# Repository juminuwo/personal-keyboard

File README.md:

# Personal Split Keyboard

A 33-key split ergonomic keyboard designed with Ergogen and KiCad.

## PCB Preview

| Left Half | Right Half |
|-----------|------------|
|  |  |

## Layout

```
Left Hand (17 keys)                    Right Hand (16 keys)

     Q     W     E     R     T              Y     U     I     O
     A   ALT_S CTL_D SFT_F   G            SFT_H CTL_J ALT_K   L     P
   GUI_Z   X     C     V     B              N     M     ,   GUI_.   /
               [LOWER] [ENTER]          [SPACE] [RAISE]
```

- 5x3 matrix per hand with staggered columns
- Right pinky top key removed (reduced pinky strain)
- 2 thumb keys per hand with splay
- Home row mods on S, D, F, H, J, K, Z, .

## Parts List

| Component | Quantity | Notes |
|-----------|----------|-------|
| **Switches** | | |
| Kailh Choc v1 switches | 33 | Low-profile, PG1350 |
| Kailh Choc hotswap sockets | 33 | CPG135001S30 |
| **Keycaps** | | |
| Choc-compatible keycaps | 33 | 18mm x 17mm spacing |
| **Electronics** | | |
| RP2040 Pro Micro | 2 | Recommended (has onboard reset/boot buttons) |
| 1N4148 diodes | 33 | Through-hole or SMD (SOD-123) |
| TRRS jack (PJ-320A) | 2 | 4-pole, for split communication |
| Tactile reset button | 2 | Optional - SMD 5.2x5.2mm (SKQGABE010) |
| **Cables & Hardware** | | |
| TRRS cable | 1 | 4-pole, any length |
| USB-C cable | 1 | For connecting to computer |
| Rubber feet | 8-10 | Self-adhesive silicone bumpers |

## PCB Specifications

| Spec | Value |
|------|-------|
| Key spacing (X) | 18mm (standard Choc) |
| Key spacing (Y) | 17mm (standard Choc) |
| Switch cutout | 13.8mm x 13.8mm |
| PCB thickness | 1.6mm (standard) |
| Layers | 2 (F.Cu, B.Cu) |

### Column Stagger

**Left Hand:**
| Finger | Stagger |
|--------|---------|
| Pinky | 0mm (baseline) |
| Ring | +5mm |
| Middle | +2.5mm |
| Index | -2.5mm |
| Inner | -2.5mm |

**Right Hand (intentionally different due to hand injury):**
| Finger | Stagger |
|--------|---------|
| Inner | +2.5mm |
| Index | +2.5mm |
| Middle | -2.5mm |
| Ring | -5mm |
| Pinky | 0mm (baseline) |

### Thumb Cluster

- Offset 27mm below index finger
- Outer thumb: 10 degrees splay
- Inner thumb: 5 degrees splay

## Build Instructions

### 1. Generate PCB Files

```bash
npx ergogen keyboard.yaml -o output
```

### 2. Open in KiCad

Open `output/pcbs/left_pcb.kicad_pcb` and `output/pcbs/right_pcb.kicad_pcb` in KiCad.

### 3. Route Traces

Complete the PCB routing in KiCad:
- Route columns on B.Cu (bottom layer)
- Route rows on F.Cu (top layer)
- Add ground pour on B.Cu
- Run DRC to check for errors

### 4. Manufacturing

Export Gerber files and submit to a PCB manufacturer:
- JLCPCB (budget, ships from China)
- Aisler (EU-based, no customs for UK/EU)
- PCBWay

### 5. Assembly Order

1. Solder diodes (observe polarity, bottom side)
2. Solder hotswap sockets (bottom side)
3. Solder TRRS jack
4. Solder reset button (optional)
5. Solder Pro Micro headers or directly
6. Insert switches into hotswap sockets
7. Add keycaps

## Firmware

This keyboard uses QMK firmware, based on my [Sofle personal keymap](https://github.com/juminuwo/sofle-personal-keymap).

### QMK File Structure

```
qmk/
├── config.h              # Keyboard-level config
├── info.json             # Keyboard definition (pins, matrix)
├── rules.mk              # Build rules
└── keymaps/
    └── default/
        ├── config.h      # Keymap-level config
        ├── keymap.c      # Keymap (based on Sofle)
        └── rules.mk      # Keymap features
```

### Keymap Layers

| Layer | Activation | Contents |
|-------|------------|----------|
| QWERTY | Default | Base layer with home row mods |
| QWERTY_PLAIN | Toggle | Base layer without home row mods |
| LOWER | Hold thumb | Numbers, symbols (!@#, {}, []) |
| RAISE | Hold thumb | Navigation (arrows), editing |
| ADJUST | LOWER+RAISE | Function keys, settings |

### Combos

| Keys | Output |
|------|--------|
| W + E | Backspace |
| U + I | Delete |
| N + M | Escape |
| C + V | Tab |

### Home Row Mods

| Key | Tap | Hold |
|-----|-----|------|
| S | s | Alt |
| D | d | Ctrl |
| F | f | Shift |
| H | h | Shift |
| J | j | Ctrl |
| K | k | Alt |
| Z | z | GUI |
| . | . | GUI |

### Pin Assignments

| Function | Left | Right |
|----------|------|-------|
| Columns (C0-C4) | GP1, GP0, GP2, GP3, GP4 | GP21, GP20, GP19, GP18, GP15 |
| Thumb cols (T0-T1) | GP5, GP6 | GP16, GP10 |
| Rows (R0-R3) | GP7, GP8, GP9, GP10 | GP9, GP8, GP7, GP6 |
| Serial (TRRS) | GP14 | GP14 |

Note: Right side uses different pins for easier PCB routing.

### Flashing Firmware

1. Copy `qmk/` folder to `qmk_firmware/keyboards/personal_split_33/`

2. Compile:
```bash
qmk compile -kb personal_split_33 -km default
```

3. Flash (put RP2040 in bootloader mode first):
```bash
qmk flash -kb personal_split_33 -km default
```

### Matrix

```
        C0    C1    C2    C3    C4    T0    T1
R0    [0,0] [0,1] [0,2] [0,3] [0,4]
R1    [1,0] [1,1] [1,2] [1,3] [1,4]
R2    [2,0] [2,1] [2,2] [2,3] [2,4]
R3                                  [3,5] [3,6]
```

## MCU Options

| Controller | Firmware | Features |
|------------|----------|----------|
| RP2040 Pro Micro | QMK | Recommended, onboard reset/boot buttons |
| ATmega32U4 Pro Micro | QMK | Classic, cheaper |
| nice!nano (nRF52840) | ZMK | Wireless/Bluetooth, battery support |

## Soldering Notes

### Equipment Needed
- Soldering iron with temperature control (320-350C)
- 0.8mm solder (60/40 rosin core or lead-free)
- Tweezers for SMD components
- Flux (optional but helpful)

### Safety
- Use ventilation or fume extractor
- Wash hands after soldering
- Don't eat/drink at workbench

## File Structure

```
personal_keyboard/
├── keyboard.yaml          # Ergogen configuration
├── README.md              # This file
├── CLAUDE.md              # Development notes
├── qmk/                   # QMK firmware
│   ├── config.h
│   ├── info.json
│   ├── rules.mk
│   └── keymaps/default/
│       ├── config.h
│       ├── keymap.c
│       └── rules.mk
└── output/
    ├── outlines/          # DXF plate files
    └── pcbs/              # KiCad PCB files
```

## License

MIT

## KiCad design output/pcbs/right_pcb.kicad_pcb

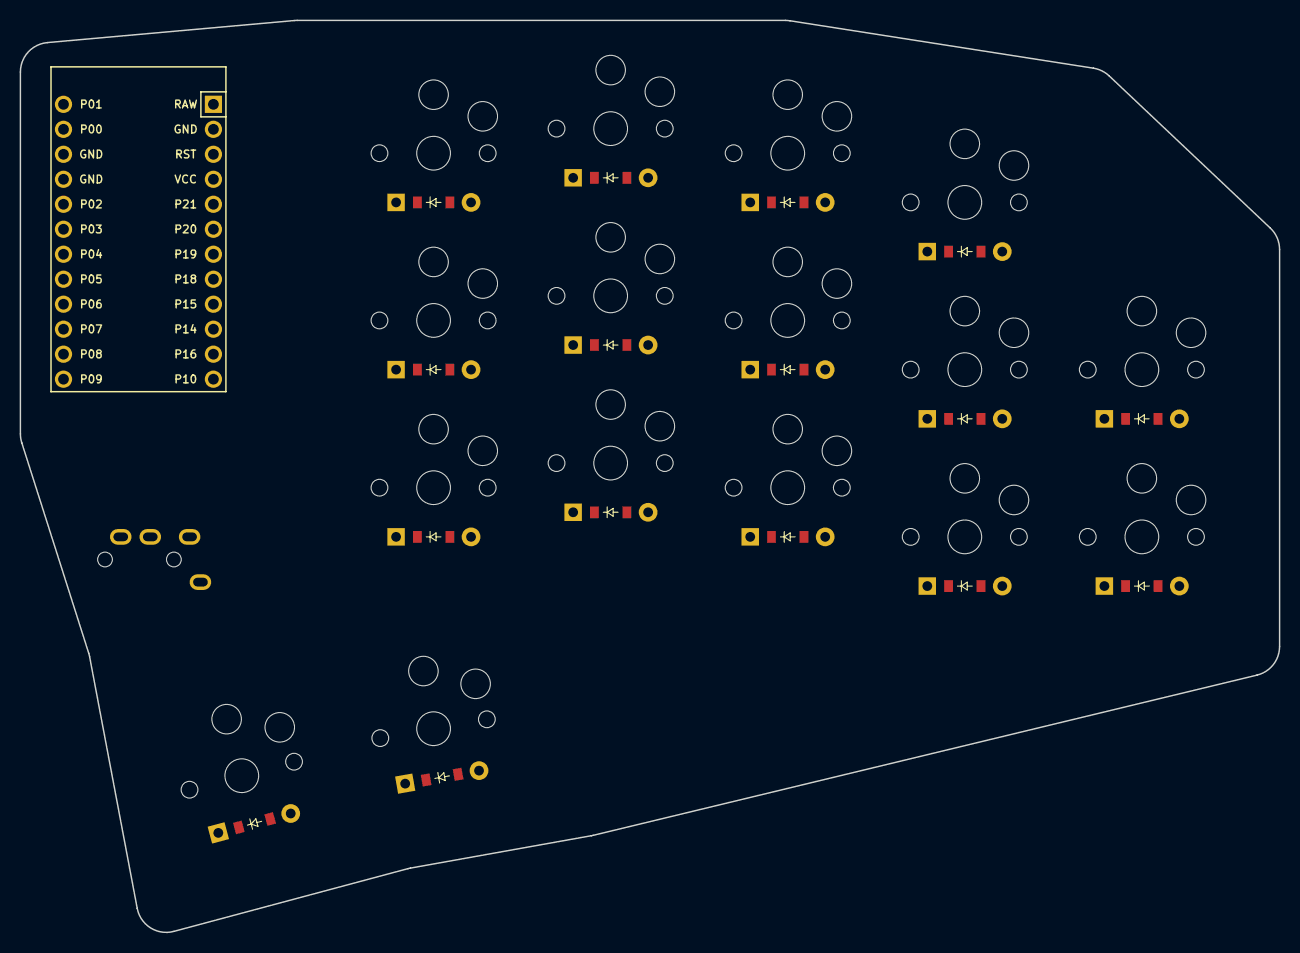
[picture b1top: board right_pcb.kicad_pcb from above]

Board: 2 copper layers, 128.0 x 92.7 mm, 34 parts (0 on the bottom side), 30 nets, no tracks yet.

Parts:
D1, D2, D3, D4, D5, D6, D7, D8, D9, D10, D11, D12, D13, D14, D15, D16: ComboDiode
MCU1: ProMicro
S1, S2, S3, S4, S5, S6, S7, S8, S9, S10, S11, S12, S13, S14, S15, S16: PG1350
TRRS1: TRRS-PJ-320A-dual

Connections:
GND: MCU1.2, MCU1.15, MCU1.16, TRRS1.1, TRRS1.2
R_C0: MCU1.5, S1.1, S2.1, S3.1
R_C1: MCU1.6, S4.1, S5.1, S6.1
R_C2: MCU1.7, S7.1, S8.1, S9.1
R_C3: MCU1.8, S10.1, S11.1, S12.1
R_C4: MCU1.9, S13.1, S14.1
R_R0: D1.2, D4.2, D7.2, D10.2, D13.2, MCU1.22
R_R1: D2.2, D5.2, D8.2, D11.2, D14.2, MCU1.23
R_R2: D3.2, D6.2, D9.2, D12.2, MCU1.24
R_R3: D15.2, D16.2, MCU1.21
R_T0: MCU1.11, S15.1
R_T1: MCU1.12, S16.1
SERIAL: MCU1.10, TRRS1.3
VCC: MCU1.1, MCU1.4, TRRS1.4
right_matrix_index_bottom: D4.1, S4.2
right_matrix_index_home: D5.1, S5.2
right_matrix_index_top: D6.1, S6.2
right_matrix_inner_bottom: D1.1, S1.2
right_matrix_inner_home: D2.1, S2.2
right_matrix_inner_top: D3.1, S3.2
right_matrix_middle_bottom: D7.1, S7.2
right_matrix_middle_home: D8.1, S8.2
right_matrix_middle_top: D9.1, S9.2
right_matrix_pinky_bottom: D13.1, S13.2
right_matrix_pinky_home: D14.1, S14.2
right_matrix_ring_bottom: D10.1, S10.2
right_matrix_ring_home: D11.1, S11.2
right_matrix_ring_top: D12.1, S12.2
right_thumb_inner_thumb: D16.1, S16.2
right_thumb_outer_thumb: D15.1, S15.2

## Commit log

2025-12-16 remove default project template files
2025-12-21 Update .gitignore, keyboard.yaml, and add README with PCB files for personal split keyboard
2025-12-21 Enhance README with PCB previews, detailed QMK file structure, keymap layers, and home row mods. Update pin assignments and flashing instructions for firmware.
2025-12-21 Update .gitignore to include specific backup directory and remove outdated personal keyboard backup zip files.
2025-12-21 Remove package.json and fp-info-cache files, and update .gitignore to include these deletions.
2026-01-09 fix spacing
2026-01-18 Refactor keyboard.yaml to remove reset button configurations, update PCB net patterns for left and right PCBs, and adjust matrix pin assignments in info.json. Enhance README with stagger details for 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
2026-05-14 docs: rename CLAUDE.md → AGENTS.md (symlink kept for Claude Code)
    AGENTS.md is the harness-neutral standard used by Codex, Cursor, Gemini,
    Copilot, Aider, and others. CLAUDE.md is kept as a symlink because Claude
    Code doesn't natively read AGENTS.md yet (anthropics/claude-code#6235).
